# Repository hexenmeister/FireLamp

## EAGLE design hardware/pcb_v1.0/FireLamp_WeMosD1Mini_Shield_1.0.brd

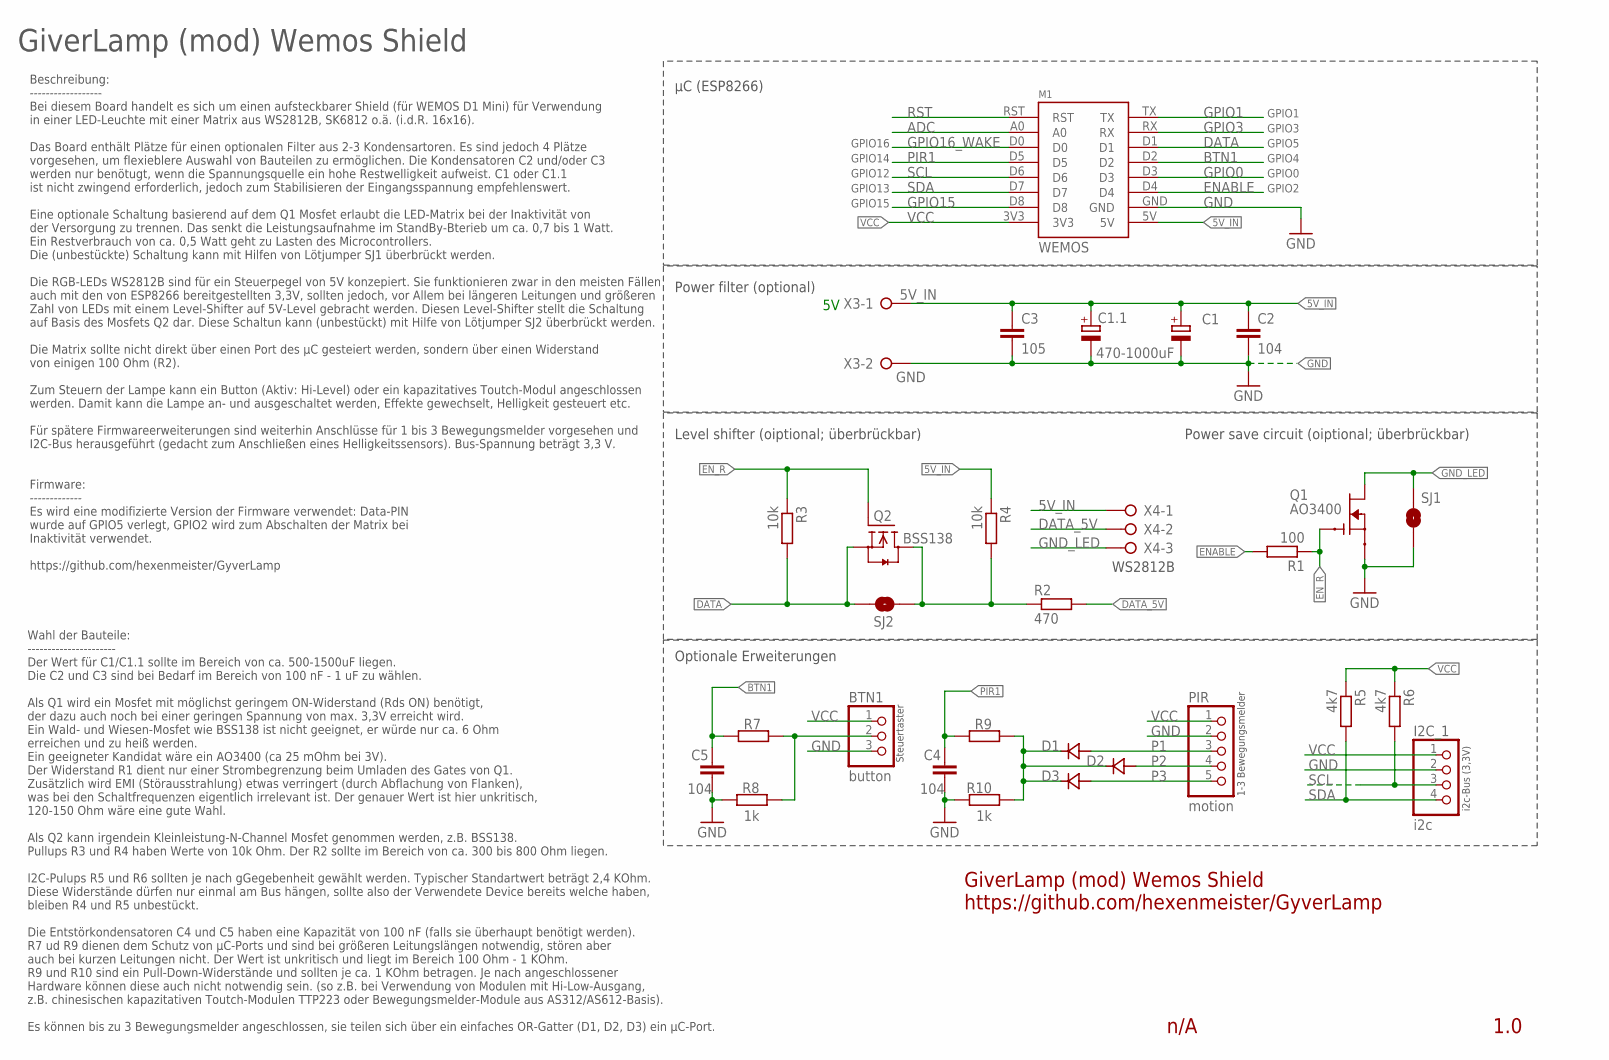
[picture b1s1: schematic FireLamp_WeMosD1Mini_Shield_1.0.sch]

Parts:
BTN1: button; 1X03
C1: 470-1000uF; E2,5-6E
C1.1: CPOL-EU140CLH-1010; 140CLH-1010
C2, C4, C5: 104; C0805
C3: 105; MY1210
D1, D2, D3: SS14; DO214
I2C_1: i2c; 1X04
M1: WEMOS
PIR: motion; 1X05
Q1: AO3400; SOT23
Q2: BSS138; SOT23
R1: 100; R0805
R2: 470; R0805
R3, R4: 10k; R0805
R5, R6: 4k7; R0805
R7, R9: 100; R0805_SMALL_GAP
R8, R10: 1k; R0805
SJ1: pwr sv; PAD-JUMPER-2-NO_YES_SILK
SJ2: lvl sh; PAD-JUMPER-2-NO_YES_SILK
X3: W237-02P; W237-132
X4: W237-03P; W237-133

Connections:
5V_IN: C1.+, C1.1.+, C2.1, C3.1, M1.5V, R4.1, X3.1, X4.1
ADC: M1.A0
BTN1: C5.1, M1.D2, R7.2
DATA: M1.D1, Q2.2 (S), R3.2, SJ2.1
DATA_5V: R2.2, X4.2
ENABLE: M1.D4, R1.2
EN_R: Q1.1 (G), Q2.1 (G), R1.1, R3.1
GND: BTN1.3, C1.-, C1.1.-, C2.2, C3.2, C4.2, C5.2, I2C_1.2, M1.GND, PIR.2, Q1.2 (S), R8.2, R10.2, SJ1.2, X3.2
GND_LED: Q1.3 (D), SJ1.1, X4.3
GPIO0: M1.D3
GPIO1: M1.TX
GPIO3: M1.RX
GPIO15: M1.D8
GPIO16_WAKE: M1.D0
unnamed: D1.CATHODE, D2.CATHODE, D3.CATHODE, R9.1, R10.1
unnamed: BTN1.2, R7.1, R8.1
unnamed: Q2.3 (D), R2.1, R4.2, SJ2.2
P1: D1.ANODE, PIR.3
P2: D2.ANODE, PIR.4
P3: D3.ANODE, PIR.5
PIR1: C4.1, M1.D5, R9.2
RST: M1.RST
SCL: I2C_1.3, M1.D6, R6.2
SDA: I2C_1.4, M1.D7, R5.2
VCC: BTN1.1, I2C_1.1, M1.3V3, PIR.1, R5.1, R6.1

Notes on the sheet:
GiverLamp (mod) Wemos Shield https://github.com/hexenmeister/GyverLamp
GiverLamp (mod) Wemos Shield
GPIO16
GPIO5
GPIO4
GPIO0
GPIO2
GPIO14
GPIO12
GPIO13
GPIO15
GPIO3
GPIO1
Beschreibung: ------------------ Bei diesem Board handelt es sich um einen aufsteckbarer Shield (für WEMOS D1 Mini) für Verwendung in einer LED-Leuchte mit einer Matrix aus WS2812B, SK6812 o.ä. (i.d.R. 16x16). Das Board enthält Plätze für einen optionalen Filter aus 2-3 Kondensartoren. Es sind jedo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
1.0
n/A
µC (ESP8266)
Power filter (optional)
Level shifter (oiptional; überbrückbar)
Power save circuit (oiptional; überbrückbar)
Optionale Erweiterungen
WS2812B
Wahl der Bauteile: ---------------------- Der Wert für C1/C1.1 sollte im Bereich von ca. 500-1500uF liegen. Die C2 und C3 sind bei Bedarf im Bereich von 100 nF - 1 uF zu wählen. Als Q1 wird ein Mosfet mit möglichst geringem ON-Widerstand (Rds ON) benötigt, der dazu auch noch bei einer geringen Span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
Steuertaster
1-3 Bewegungsmelder
i2c-Bus (3,3V)

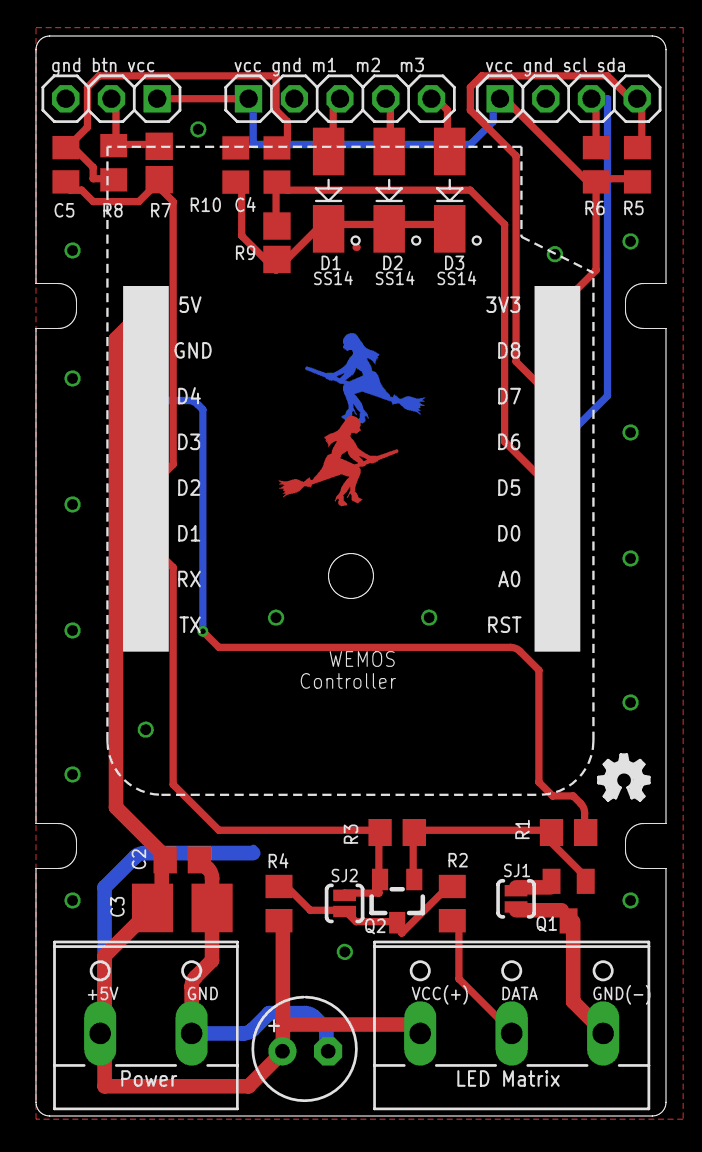
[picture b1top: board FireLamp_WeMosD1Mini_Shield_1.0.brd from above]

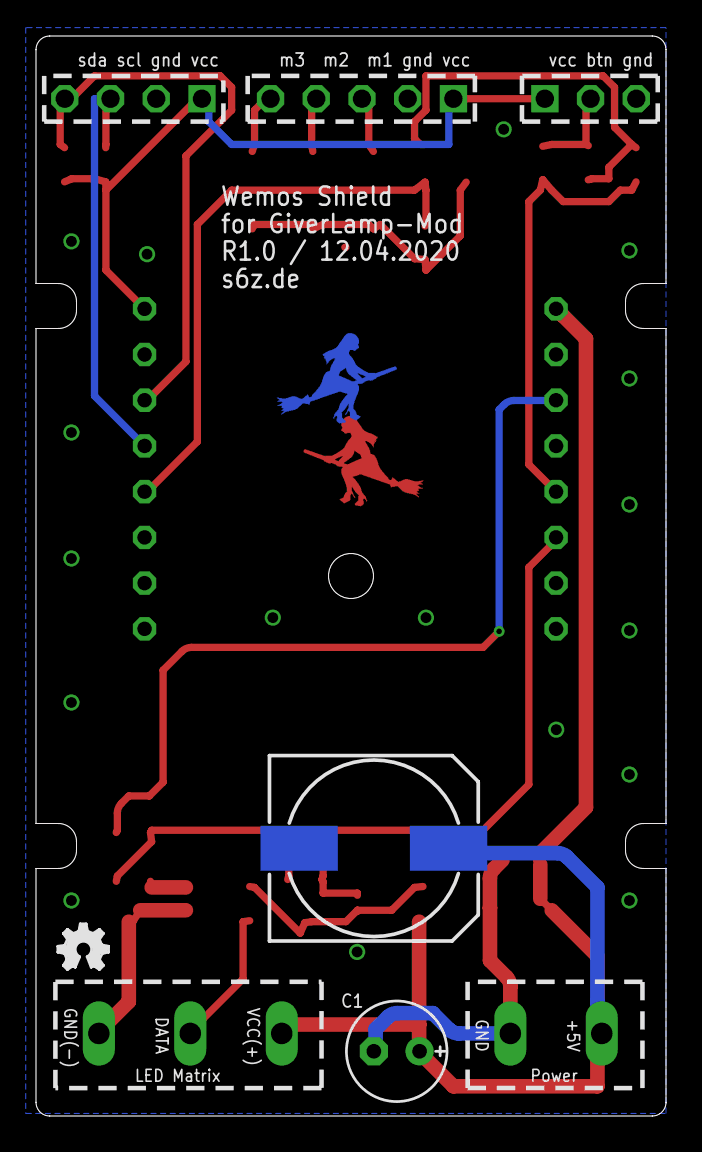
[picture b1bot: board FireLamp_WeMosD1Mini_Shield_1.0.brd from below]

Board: 2 copper layers, 35.0 x 60.0 mm, 31 parts (3 on the bottom side), 18 nets.

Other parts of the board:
U$1, U$2: OSHW_FILLX100_NOTEXT

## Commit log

2020-04-19 old versions removed
2020-04-19 initial
2020-04-19 added effects: cloud / thunder in the jar
2020-04-20 no reset settings
2020-04-20 added web server control
2020-04-21 added: http update server controls
2020-04-23 added Effect Twinkles
2020-04-29 Korrektur
2020-05-02 new effects data storage
2020-05-04 improved get effects json
2020-05-04 prepare to sysconfig etc.
2020-05-06 reset
2020-12-28 change: ntp server adress / matrix angle
2020-12-29 Test

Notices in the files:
parts and their libraries:
SparkFun-Passives: Licensing: Creative Commons ShareAlike 4.0 International - https://creativecommons.org/licenses/by-sa/4.0
